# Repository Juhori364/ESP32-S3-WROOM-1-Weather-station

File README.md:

# ESP32-S3-WROOM-1-Weather-station

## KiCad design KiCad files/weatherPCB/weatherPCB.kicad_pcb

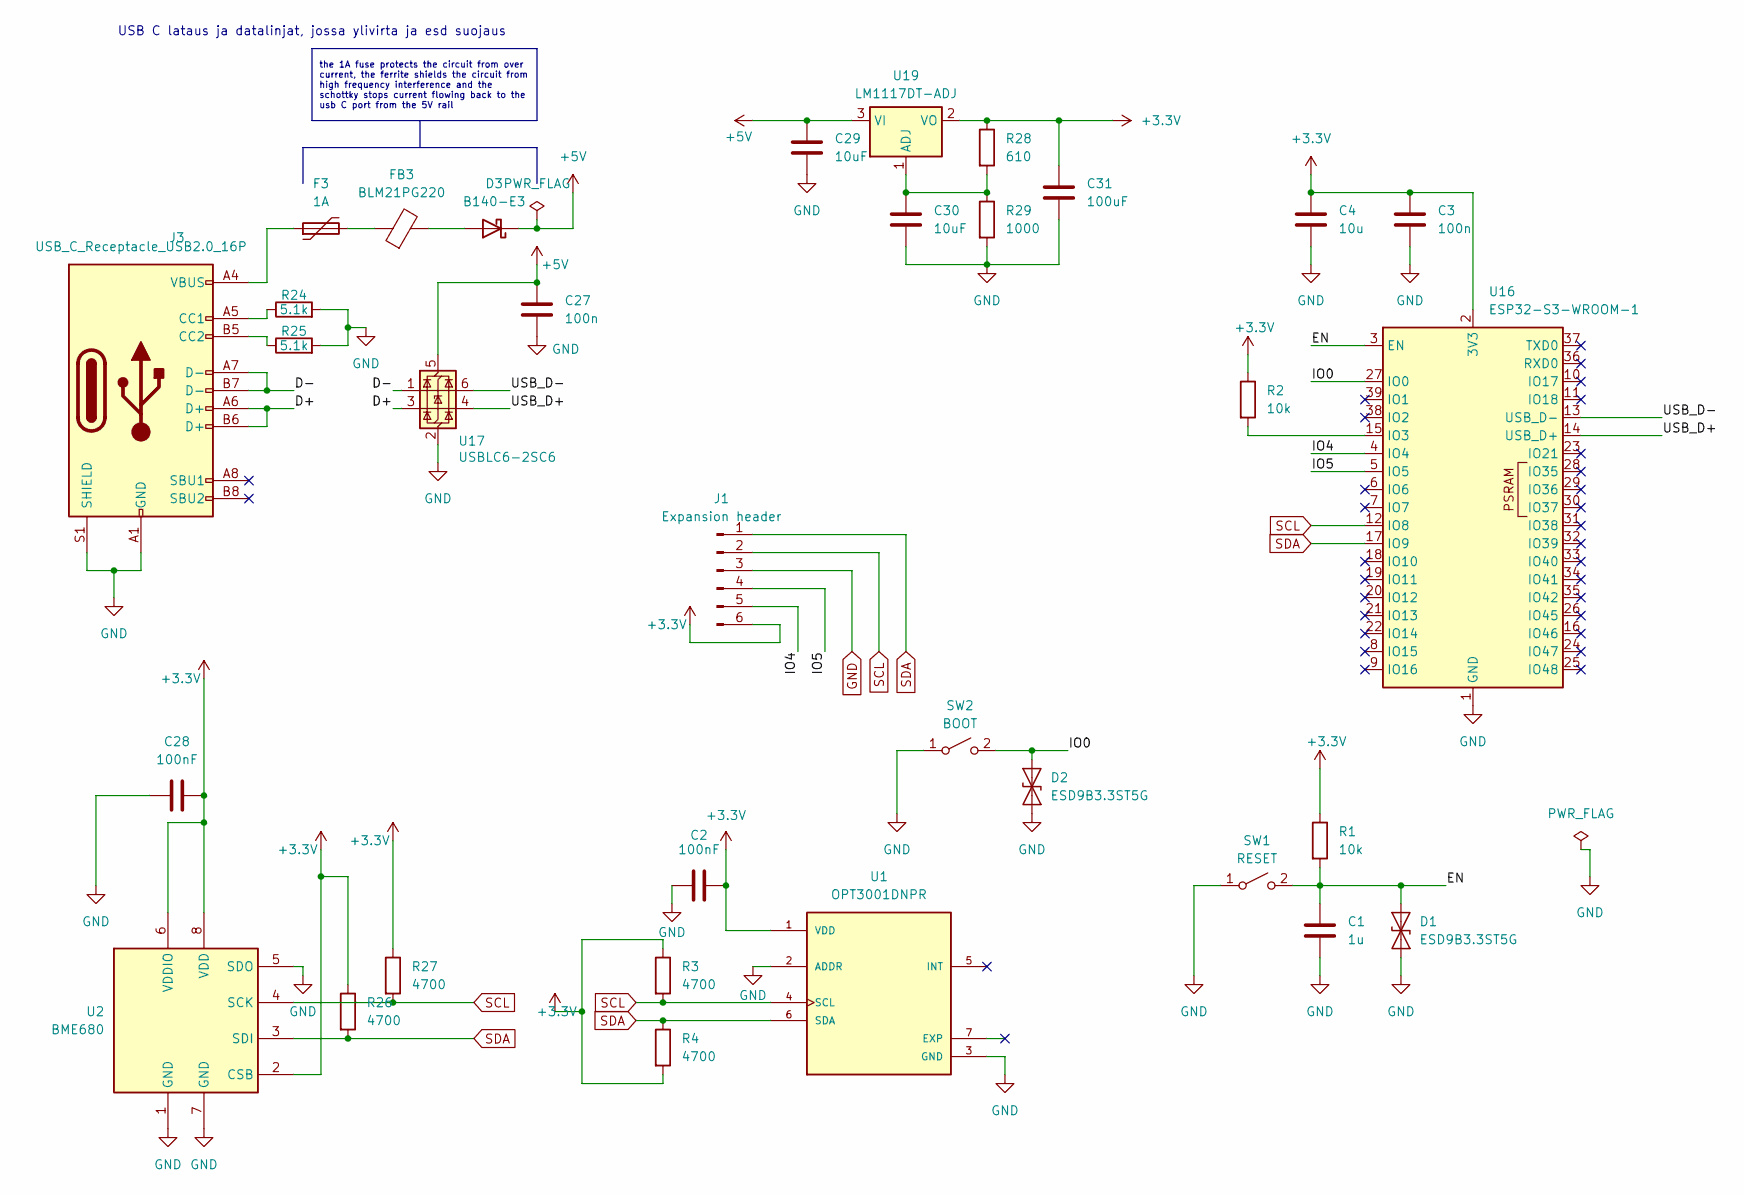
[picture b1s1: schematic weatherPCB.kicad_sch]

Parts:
C1: 1u; C_0805_2012Metric
C2, C28: 100nF; C_0805_2012Metric
C3, C27: 100n; C_0805_2012Metric
C4: 10u; C_0805_2012Metric
C29, C30: 10uF; C_0805_2012Metric
C31: 100uF; C_0805_2012Metric
D1, D2: ESD9B3.3ST5G; D_SOD-923
D3: B140-E3; D_SMA
F3: 1A; Fuse_1206_3216Metric
FB3: BLM21PG220; L_0805_2012Metric
J1: Expansion header; PinHeader_1x06_P2.54mm_Vertical_SMD_Pin1Left
J3: USB_C_Receptacle_USB2.0_16P; USB_C_Receptacle_GCT_USB4105-xx-A_16P_TopMnt_Horizontal
R1, R2: 10k; R_0805_2012Metric
R3, R4, R26, R27: 4700; R_0805_2012Metric
R24, R25: 5.1k; R_0805_2012Metric
R28: 610; R_0805_2012Metric
R29: 1000; R_0805_2012Metric
SW1: RESET; SW_SPST_B3U-1000P
SW2: BOOT; SW_SPST_B3U-1000P
U1: OPT3001DNPR; SON65P200X200X65-7N
U2: BME680; Bosch_LGA-8_3x3mm_P0.8mm_ClockwisePinNumbering
U16: ESP32-S3-WROOM-1
U17: USBLC6-2SC6; SOT-23-6
U19: LM1117DT-ADJ; TO-252-3_TabPin2

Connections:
+3.3V: C2.2, C3.1, C4.1, C28.2, C31.1, J1.6, R1.1, R2.1, R3.1, R4.2, R26.1, R27.1, R28.1, U1.1 (VDD), U2.2 (CSB), U2.6 (VDDIO), U2.8 (VDD), U16.2 (3V3), U19.2 (VO)
+5V: C27.1, C29.1, D3.1 (K), U17.5 (VBUS), U19.3 (VI)
/D+: J3.A6 (D+), J3.B6 (D+), U17.3 (I/O2)
/D-: J3.A7 (D-), J3.B7 (D-), U17.1 (I/O1)
/EN: C1.2, D1.2 (A2), R1.2, SW1.2 (B), U16.3 (EN)
/IO0: D2.2 (A2), SW2.2 (B), U16.27 (IO0)
/IO4: J1.5, U16.4 (IO4)
/IO5: J1.4, U16.5 (IO5)
/USB_D+: U16.14 (USB_D+), U17.4 (I/O2)
/USB_D-: U16.13 (USB_D-), U17.6 (I/O1)
GND: C1.1, C2.1, C3.2, C4.2, C27.2, C28.1, C29.2, C30.2, C31.2, D1.1 (A1), D2.1 (A1), J1.3, J3.A1 (GND), J3.A12 (GND), J3.B1 (GND), J3.B12 (GND), J3.S1 (SHIELD), R24.2, R25.2, R29.2, SW1.1 (A), SW2.1 (A), U1.2 (ADDR), U1.3 (GND), U2.1 (GND), U2.5 (SDO), U2.7 (GND), U16.1 (GND), U16.40 (GND), U16.41 (GND), U17.2 (GND)
unnamed: D3.2 (A), FB3.2
unnamed: F3.1, J3.A4 (VBUS), J3.A9 (VBUS), J3.B4 (VBUS), J3.B9 (VBUS)
unnamed: F3.2, FB3.1
unnamed: J3.A5 (CC1), R24.1
unnamed: J3.B5 (CC2), R25.1
unnamed: R2.2, U16.15 (IO3)
unnamed: C30.1, R28.2, R29.1, U19.1 (ADJ)
SCL: J1.2, R3.2, R27.2, U1.4 (SCL), U2.4 (SCK), U16.12 (IO8)
SDA: J1.1, R4.1, R26.2, U1.6 (SDA), U2.3 (SDI), U16.17 (IO9)

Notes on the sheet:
USB C lataus ja datalinjat, jossa ylivirta ja esd suojaus
the 1A fuse protects the circuit from over current, the ferrite shields the circuit from high frequency interference and the schottky stops current flowing back to the usb C port from the 5V rail

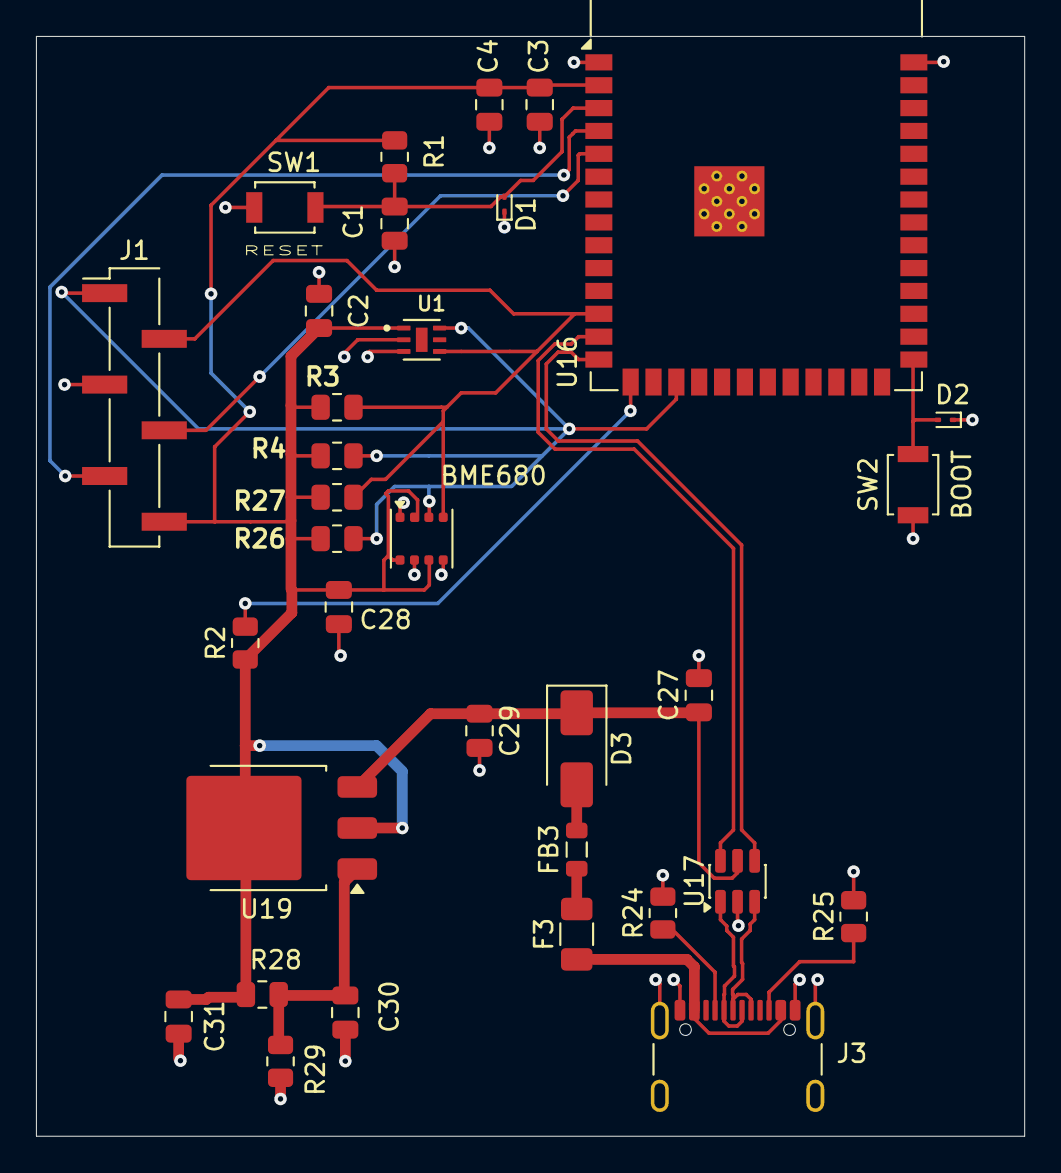
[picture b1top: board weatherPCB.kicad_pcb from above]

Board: 2 copper layers, 54.9 x 61.1 mm, 33 parts (0 on the bottom side), 20 nets.

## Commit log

2026-03-20 Initial project setup. ESP32 database connection done.
2026-03-20 reorganized api files
2026-03-24 Added KiCad files
2026-03-25 Added expansion header schematic
2026-03-29 Added KiCad PCB files, removed outdated files
2026-03-30 Improved usb routing on pcb
2026-03-30 replaced bme280 with bme680
2026-03-30 Corrected error with solder mask
2026-04-21 Erilliskehtiys
2026-04-21 Koodi toimii piirilevylla
2026-04-25 molempien sensoreiden mittauskoodi lisätty
2026-04-27 Added functionalities for sending sensor values to db and displaying current values on OLED.
2026-04-27 Revert "Added functionalities for sending sensor values to db and displaying current values on OLED."
    This reverts commit 44f47b590dcc303441a32ba9328aefa91a15b14d.
2026-04-27 Added wifi and display functionalities to ESP32weatherStation.ino
2026-04-30 added i2c scanner that we used
